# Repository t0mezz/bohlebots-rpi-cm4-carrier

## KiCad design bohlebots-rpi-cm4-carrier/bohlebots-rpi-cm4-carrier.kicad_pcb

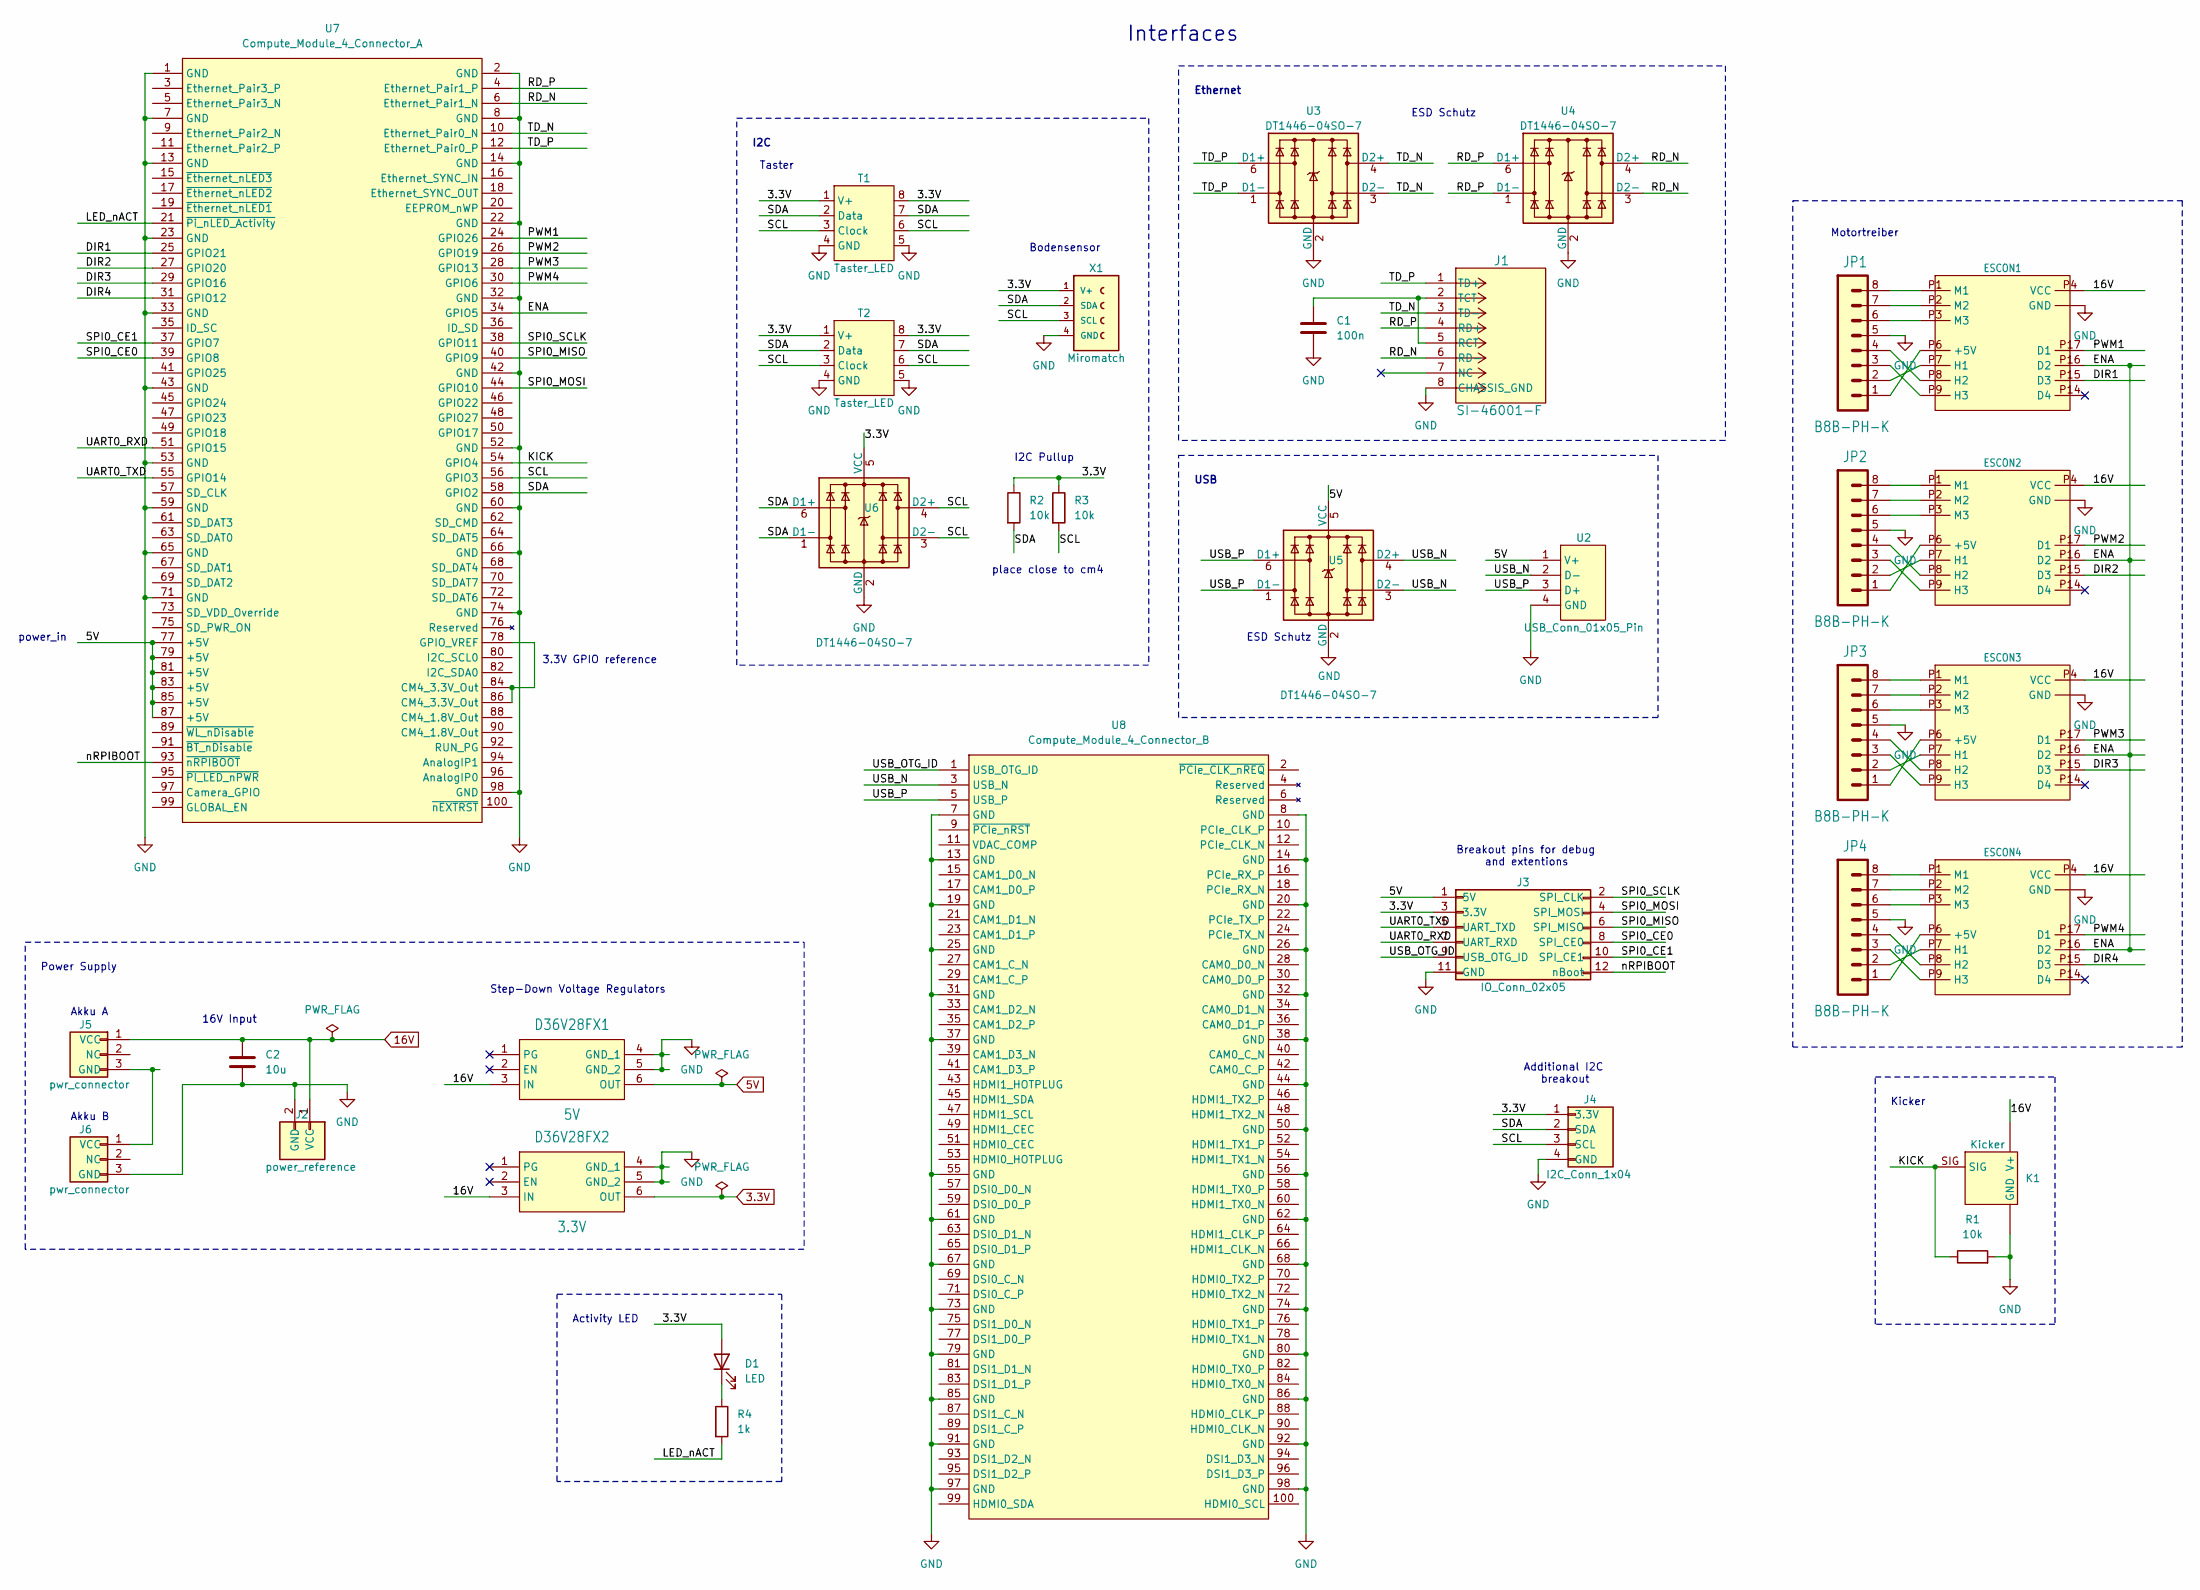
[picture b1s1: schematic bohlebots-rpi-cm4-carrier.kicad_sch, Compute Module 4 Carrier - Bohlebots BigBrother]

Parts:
C1: 100n; C_Radial_D5.0mm_H11.0mm_P2.00mm
C2: 10u; C_Radial_D5.0mm_H11.0mm_P2.00mm
D1: LED; LED_D5.0mm_FlatTop
D36V28FX1: 5V; D36V28FX
D36V28FX2: 3.3V; D36V28FX
ESCON1, ESCON2, ESCON3, ESCON4: 24_2; ESCOM_24_2
J1: SI-46001-F; CONN_46001-F_BEL
J2: power_reference; PinHeader_1x02_P2.54mm_Vertical
J3: IO_Conn_02x05; PinHeader_2x06_P2.54mm_Vertical
J4: I2C_Conn_1x04; PinHeader_1x04_P2.54mm_Vertical
J5, J6: pwr_connector; PinHeader_1x03_P2.54mm_Vertical
JP1, JP2, JP3, JP4: B8B-PH-K
K1: Kicker; KICKER
R1, R2, R3: 10k; R_Axial_DIN0207_L6.3mm_D2.5mm_P7.62mm_Horizontal
R4: 1k; R_Axial_DIN0207_L6.3mm_D2.5mm_P7.62mm_Horizontal
T1, T2: Taster_LED; TASTER_LED
U2: USB_Conn_01x05_Pin; PinHeader_1x04_P2.54mm_Vertical
U3, U4, U5, U6: DT1446-04SO-7; SOT26; Part Description Quad TVS diode for high speed signals (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
U7: Compute_Module_4_Connector_A; Hirose-DF40C-100DS-0.4V(51)
U8: Compute_Module_4_Connector_B; Hirose-DF40C-100DS-0.4V(51)
X1: Miromatch; MICROMATCH-4

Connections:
3.3V: D1.2 (A), D36V28FX2.6 (OUT), J3.3 (3.3V), J4.1 (3.3V), R2.1, R3.1, T1.1 (V+), T1.8, T2.1 (V+), T2.8, U6.5 (VCC), X1.1 (V+)
5V: D36V28FX1.6 (OUT), J3.1 (5V), U2.1 (V+), U5.5 (VCC), U7.77 (+5V), U7.79 (+5V), U7.81 (+5V), U7.83 (+5V), U7.85 (+5V), U7.87 (+5V)
16V: C2.1, D36V28FX1.3 (IN), D36V28FX2.3 (IN), ESCON1.P4 (VCC), ESCON2.P4 (VCC), ESCON3.P4 (VCC), ESCON4.P4 (VCC), J2.1 (VCC), J5.1 (VCC), K1.V+1 (V+), K1.V+2 (V+), K1.V+3 (V+)
/DIR1: ESCON1.P15 (D3), U7.25 (GPIO21)
/DIR2: ESCON2.P15 (D3), U7.27 (GPIO20)
/DIR3: ESCON3.P15 (D3), U7.29 (GPIO16)
/DIR4: ESCON4.P15 (D3), U7.31 (GPIO12)
/ENA: ESCON1.P16 (D2), ESCON2.P16 (D2), ESCON3.P16 (D2), ESCON4.P16 (D2), U7.34 (GPIO5)
/KICK: K1.SIG, R1.1, U7.54 (GPIO4)
/LED_nACT: R4.2, U7.21 (~Pi_nLED_Activity)
/PWM1: ESCON1.P17 (D1), U7.24 (GPIO26)
/PWM2: ESCON2.P17 (D1), U7.26 (GPIO19)
/PWM3: ESCON3.P17 (D1), U7.28 (GPIO13)
/PWM4: ESCON4.P17 (D1), U7.30 (GPIO6)
/RD_N: J1.6 (RD-), U4.3 (D2-), U4.4 (D2+), U7.6 (Ethernet_Pair1_N)
/RD_P: J1.4 (RD+), U4.1 (D1-), U4.6 (D1+), U7.4 (Ethernet_Pair1_P)
/SCL: J4.3 (SCL), R3.2, T1.3 (Clock), T1.6, T2.3 (Clock), T2.6, U6.3 (D2-), U6.4 (D2+), U7.56 (GPIO3), X1.3 (SCL)
/SDA: J4.2 (SDA), R2.2, T1.2 (Data), T1.7, T2.2 (Data), T2.7, U6.1 (D1-), U6.6 (D1+), U7.58 (GPIO2), X1.2 (SDA)
/SPI0_CE0: J3.8 (SPI_CE0), U7.39 (GPIO8)
/SPI0_CE1: J3.10 (SPI_CE1), U7.37 (GPIO7)
/SPI0_MISO: J3.6 (SPI_MISO), U7.40 (GPIO9)
/SPI0_MOSI: J3.4 (SPI_MOSI), U7.44 (GPIO10)
/SPI0_SCLK: J3.2 (SPI_CLK), U7.38 (GPIO11)
/TD_N: J1.3 (TD-), U3.3 (D2-), U3.4 (D2+), U7.10 (Ethernet_Pair0_N)
/TD_P: J1.1 (TD+), U3.1 (D1-), U3.6 (D1+), U7.12 (Ethernet_Pair0_P)
/UART0_RXD: J3.7 (UART_RXD), U7.51 (GPIO15)
/UART0_TXD: J3.5 (UART_TXD), U7.55 (GPIO14)
/USB_N: U2.2 (D-), U5.3 (D2-), U5.4 (D2+), U8.3 (USB_N)
/USB_OTG_ID: J3.9 (USB_OTG_ID), U8.1 (USB_OTG_ID)
/USB_P: U2.3 (D+), U5.1 (D1-), U5.6 (D1+), U8.5 (USB_P)
/nRPIBOOT: J3.12 (nBoot), U7.93 (~nRPIBOOT)
GND: C1.2, C2.2, D36V28FX1.4 (GND_1), D36V28FX1.5 (GND_2), D36V28FX2.4 (GND_1), D36V28FX2.5 (GND_2), ESCON1.P5 (GND), ESCON1.P18 (GND), ESCON2.P5 (GND), ESCON2.P18 (GND), ESCON3.P5 (GND), ESCON3.P18 (GND), ESCON4.P5 (GND), ESCON4.P18 (GND), J1.8 (CHASSIS_GND), J2.2 (GND), J3.11 (GND), J4.4 (GND), J6.3 (GND), JP1.5, JP2.5, JP3.5, JP4.5, K1.GND1 (GND), K1.GND2 (GND), K1.GND3 (GND), K1.GND4 (GND), K1.GND5 (GND), K1.GND6 (GND), K1.GND7 (GND), K1.GND8 (GND), R1.2, T1.4 (GND), T1.5, T2.4 (GND), T2.5, U2.4 (GND), U3.2 (GND), U4.2 (GND), U5.2 (GND), U6.2 (GND), U7.1 (GND), U7.2 (GND), U7.7 (GND), U7.8 (GND), U7.13 (GND), U7.14 (GND), U7.22 (GND), U7.23 (GND), U7.32 (GND), U7.33 (GND), U7.42 (GND), U7.43 (GND), U7.52 (GND), U7.53 (GND), U7.59 (GND), U7.60 (GND), U7.65 (GND), U7.66 (GND), U7.71 (GND), U7.74 (GND), U7.98 (GND), U8.7 (GND), U8.8 (GND), U8.13 (GND), U8.14 (GND), U8.19 (GND), U8.20 (GND), U8.25 (GND), U8.26 (GND), U8.31 (GND), U8.32 (GND), U8.37 (GND), U8.38 (GND), U8.44 (GND), U8.50 (GND), U8.55 (GND), U8.56 (GND), U8.61 (GND), U8.62 (GND), U8.67 (GND), U8.68 (GND), U8.73 (GND), U8.74 (GND), U8.79 (GND), U8.80 (GND), U8.85 (GND), U8.86 (GND), U8.91 (GND), U8.92 (GND), U8.97 (GND), U8.98 (GND), X1.4 (GND)
unnamed: D1.1 (K), R4.1
unnamed: ESCON1.P6 (+5V), JP1.1
unnamed: ESCON1.P7 (H1), JP1.2
unnamed: ESCON1.P8 (H2), JP1.4
unnamed: ESCON1.P9 (H3), JP1.3
unnamed: ESCON1.P1 (M1), JP1.8
unnamed: ESCON1.P2 (M2), JP1.7
unnamed: ESCON1.P3 (M3), JP1.6
unnamed: ESCON2.P6 (+5V), JP2.1
unnamed: ESCON2.P7 (H1), JP2.2
unnamed: ESCON2.P8 (H2), JP2.4
unnamed: ESCON2.P9 (H3), JP2.3
unnamed: ESCON2.P1 (M1), JP2.8
unnamed: ESCON2.P2 (M2), JP2.7
unnamed: ESCON2.P3 (M3), JP2.6
unnamed: ESCON3.P6 (+5V), JP3.1
unnamed: ESCON3.P7 (H1), JP3.2
unnamed: ESCON3.P8 (H2), JP3.4
unnamed: ESCON3.P9 (H3), JP3.3
unnamed: ESCON3.P1 (M1), JP3.8
unnamed: ESCON3.P2 (M2), JP3.7
unnamed: ESCON3.P3 (M3), JP3.6
unnamed: ESCON4.P6 (+5V), JP4.1
unnamed: ESCON4.P7 (H1), JP4.2
unnamed: ESCON4.P8 (H2), JP4.4
unnamed: ESCON4.P9 (H3), JP4.3
unnamed: ESCON4.P1 (M1), JP4.8
unnamed: ESCON4.P2 (M2), JP4.7
unnamed: ESCON4.P3 (M3), JP4.6
unnamed: C1.1, J1.2 (TCT), J1.5 (RCT)
unnamed: J5.3 (GND), J6.1 (VCC)
unnamed: U7.78 (GPIO_VREF), U7.84 (CM4_3.3V_Out), U7.86 (CM4_3.3V_Out)

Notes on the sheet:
ESD Schutz
Taster
USB
Power Supply
Interfaces
Bodensensor
Motortreiber
I2C Pullup
Akku B
Kicker
Ethernet
Breakout pins for debug and extentions
place close to cm4
Activity LED
3.3V GPIO reference
Akku A
power_in
I2C
Step-Down Voltage Regulators
Additional I2C breakout
16V Input

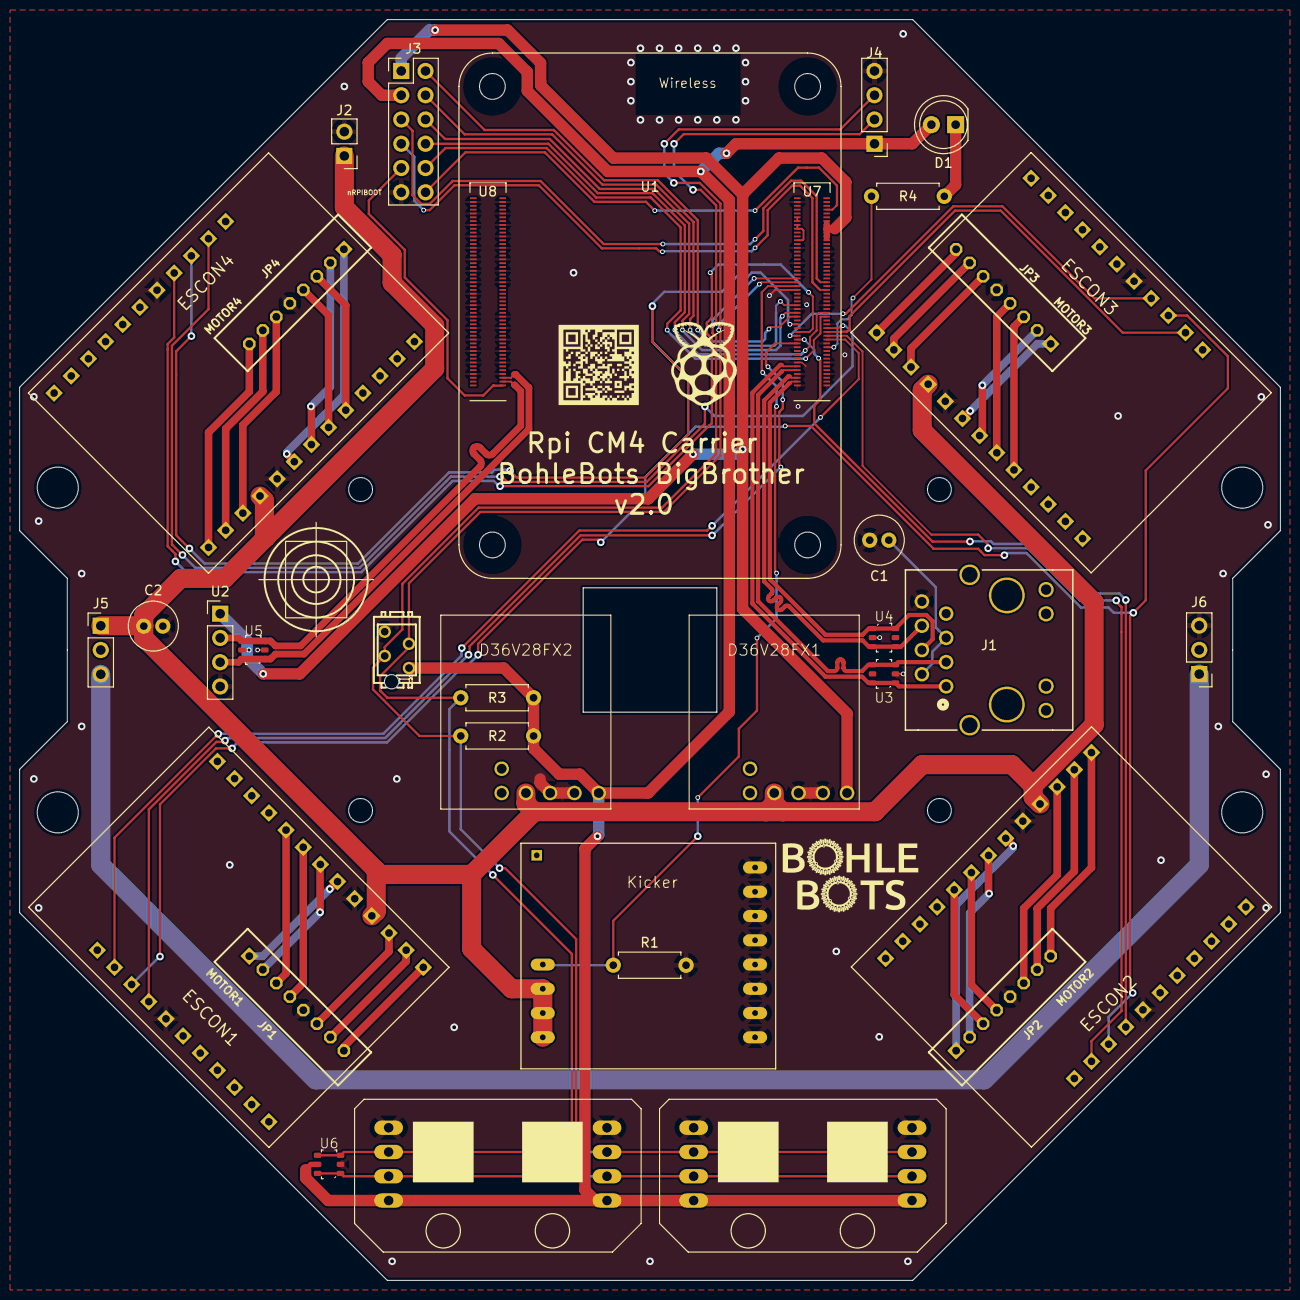
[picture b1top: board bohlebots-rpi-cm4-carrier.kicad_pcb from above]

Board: 2 copper layers, 132.0 x 132.0 mm, 37 parts (0 on the bottom side), 64 nets.

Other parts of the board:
Luxonis OAK-FFP 4P: Luxonis_OAK-FFC-4P_Foothold
REFe: MountingHole_4.3mm_M4
U1: Compute_Module_4_Connectors; Raspberry-Pi-4-Compute-Module

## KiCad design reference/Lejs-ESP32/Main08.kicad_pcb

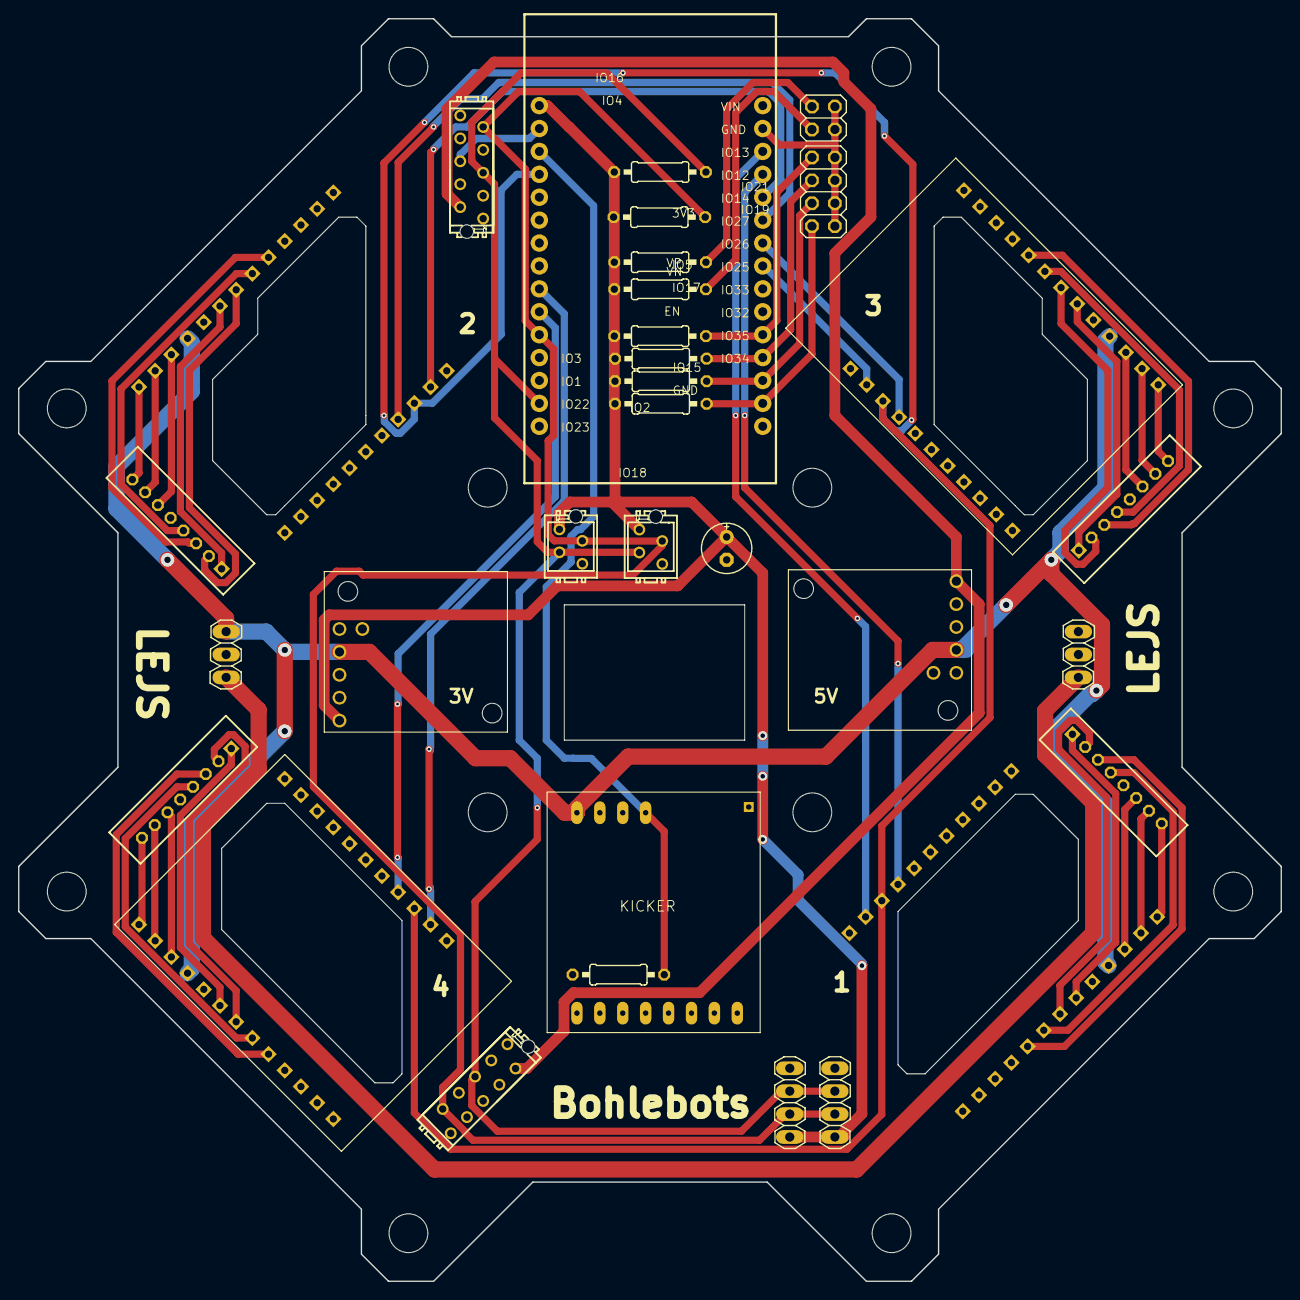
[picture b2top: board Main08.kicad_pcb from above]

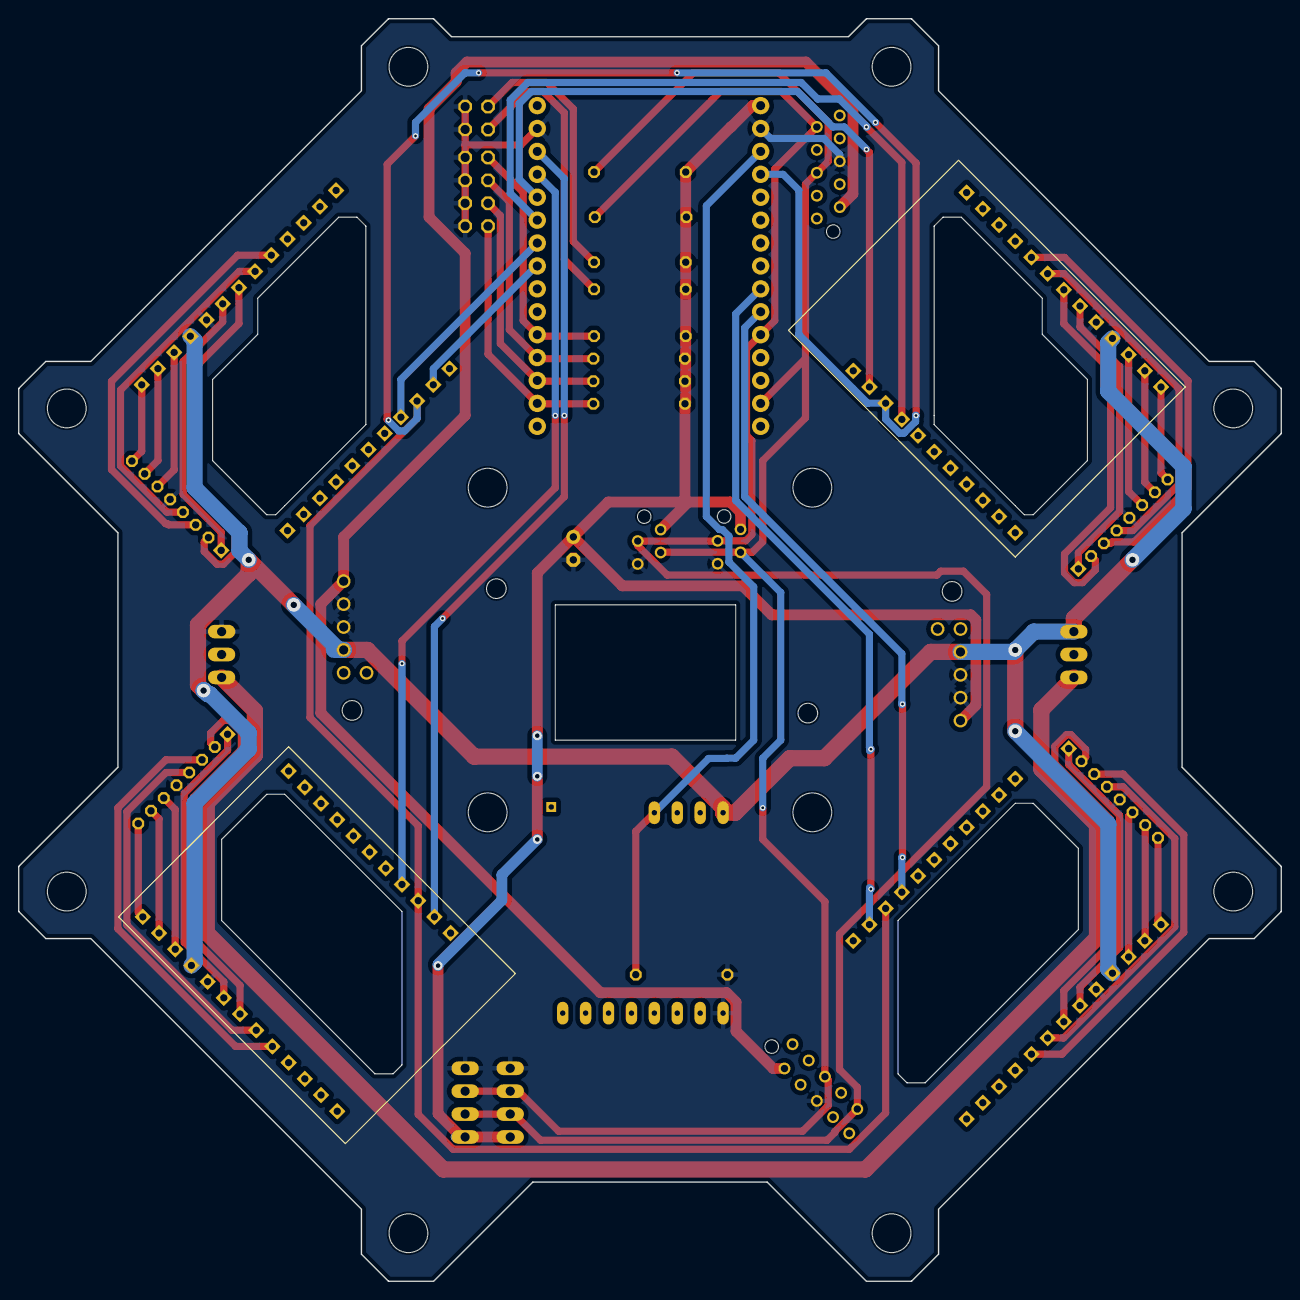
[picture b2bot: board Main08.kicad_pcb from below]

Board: 2 copper layers, 140.0 x 140.0 mm, 32 parts (2 on the bottom side), 51 nets.

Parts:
C1: 10µ; E2,5-6E
I2C_2, I2C_3: i2c-Bus; 1X04
IC1: D36V28FX; D36V28FX_3v
IC2: D36V28FX; D36V28FX_5V
JP1, JP4: Buchse; 1X03_8V
JP5, JP6, JP7, JP8: B8B-PH-K; B8B-PH-K_MS
JP13: led_out; 2X02_LS
JP14: Ana.input; 2X04_aP
R1, R2: 100; 0207_10_R
R3, R4, R5, R6, R9, R101: 10k; 0207_10_R
R108: 10K; 0207_10_R
U$1, U$2, U$3, U$4: 24/2; 24_2_MT
U$9: ESP32DEVKITV1; ESP32-DEVKITV1
U$17: KICKER
X1, X3: MICROMATCH-4; MICROMATCH-4_IR
X2, X5: MICROMATCH-10; MICROMATCH-10_Pixy

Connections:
+3V3: C1.+, I2C_2.1, I2C_3.1, IC1.6 (OUT), R1.1, R2.1, R3.1, R4.1, R5.1, R6.1, R9.1, R108.1, U$9.1 (3V3), X1.1 (S), X3.1 (S)
+5V: IC2.6 (OUT), X2.2 (S), X5.2 (S)
/CLOCK: I2C_2.3, I2C_3.3, R108.2, U$9.14 (IO22), X1.3 (S), X2.5 (S), X3.3 (S), X5.5 (S)
/DATA: I2C_2.2, I2C_3.2, R9.2, U$9.11 (IO21), X1.2 (S), X2.9 (S), X3.2 (S), X5.9 (S)
/DIR1: U$1.P15 (D3), U$9.28 (IO13)
/DIR2: U$2.P15 (D3), U$9.26 (IO14)
/DIR3: U$3.P15 (D3), U$9.23 (IO25)
/DIR4: U$4.P15 (D3), U$9.9 (IO18)
/ENA: U$1.P16 (D2), U$2.P16 (D2), U$3.P16 (D2), U$4.P16 (D2), U$9.4 (IO2)
/KICK: R101.1, U$9.3 (IO15), U$17.SIG
/PWM1: U$1.P17 (D1), U$9.27 (IO12)
/PWM2: U$2.P17 (D1), U$9.25 (IO27)
/PWM3: U$3.P17 (D1), U$9.24 (IO26)
/PWM4: U$4.P17 (D1), U$9.10 (IO19)
GND: C1.-, I2C_2.4, I2C_3.4, IC1.4 (GND_1), IC1.5 (GND_2), IC2.4 (GND_1), IC2.5 (GND_2), JP4.3, JP5.5, JP6.5, JP7.5, JP8.5, JP13.1, JP13.3, JP14.2, JP14.4, JP14.6, JP14.8, R101.2, U$1.P5 (GND), U$2.P5 (GND), U$3.P5 (GND), U$4.P5 (GND), U$9.2 (GND), U$9.29 (GND1), U$17.GND8 (GND), X1.4 (S), X2.6 (S), X3.4 (S), X5.6 (S)
unnamed: JP1.3, JP4.1
unnamed: JP13.2, R2.2
unnamed: JP13.4, R1.2
unnamed: JP5.1, U$1.P6 (+5V)
unnamed: JP5.2, U$1.P7 (H1)
unnamed: JP5.4, U$1.P8 (H2)
unnamed: JP5.3, U$1.P9 (H3)
unnamed: JP5.8, U$1.P1 (M1)
unnamed: JP5.7, U$1.P2 (M2)
unnamed: JP5.6, U$1.P3 (M3)
unnamed: JP6.1, U$2.P6 (+5V)
unnamed: JP6.2, U$2.P7 (H1)
unnamed: JP6.4, U$2.P8 (H2)
unnamed: JP6.3, U$2.P9 (H3)
unnamed: JP6.8, U$2.P1 (M1)
unnamed: JP6.7, U$2.P2 (M2)
unnamed: JP6.6, U$2.P3 (M3)
unnamed: JP7.1, U$3.P6 (+5V)
unnamed: JP7.2, U$3.P7 (H1)
unnamed: JP7.4, U$3.P8 (H2)
unnamed: JP7.3, U$3.P9 (H3)
unnamed: JP7.8, U$3.P1 (M1)
unnamed: JP7.7, U$3.P2 (M2)
unnamed: JP7.6, U$3.P3 (M3)
unnamed: JP8.1, U$4.P6 (+5V)
unnamed: JP8.2, U$4.P7 (H1)
unnamed: JP8.4, U$4.P8 (H2)
unnamed: JP8.3, U$4.P9 (H3)
unnamed: JP8.8, U$4.P1 (M1)
unnamed: JP8.7, U$4.P2 (M2)
unnamed: JP8.6, U$4.P3 (M3)
unnamed: JP14.3, R5.2, U$9.19 (IO34)
unnamed: JP14.1, R6.2, U$9.20 (IO35)
unnamed: JP14.5, R4.2, U$9.18 (VN)
unnamed: JP14.7, R3.2, U$9.17 (VP)
VCC: IC1.3 (IN), IC2.3 (IN), JP1.1, U$1.P4 (VCC), U$2.P4 (VCC), U$3.P4 (VCC), U$4.P4 (VCC), U$17.V+3 (V+)

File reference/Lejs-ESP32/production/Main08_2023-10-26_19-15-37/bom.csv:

Designator,Footprint,Quantity,Value,LCSC Part #
C1,"E2,5-6E",1,10µ,
"I2C_2, I2C_3",1X04,2,i2c-Bus,
IC1,D36V28FX_3v,1,D36V28FX,
IC2,D36V28FX_5V,1,D36V28FX,
"JP1, JP4",1X03_8V,2,Buchse,
JP13,2X02_LS,1,led_out,
JP14,2X04_aP,1,Ana.input,
"JP5, JP6, JP7, JP8",B8B-PH-K_MS,4,B8B-PH-K,
"R1, R2",0207_10_R,2,100,
"R101, R108, R3, R4, R5, R6, R9",0207_10_R,7,10k,
"U$1, U$2, U$3, U$4",24_2_MT,4,24/2,
U$17,KICKER,1,KICKER,
U$9,ESP32-DEVKITV1,1,ESP32DEVKITV1,
"X1, X3",MICROMATCH-4_IR,2,MICROMATCH-4,
"X2, X5",MICROMATCH-10_Pixy,2,MICROMATCH-10,

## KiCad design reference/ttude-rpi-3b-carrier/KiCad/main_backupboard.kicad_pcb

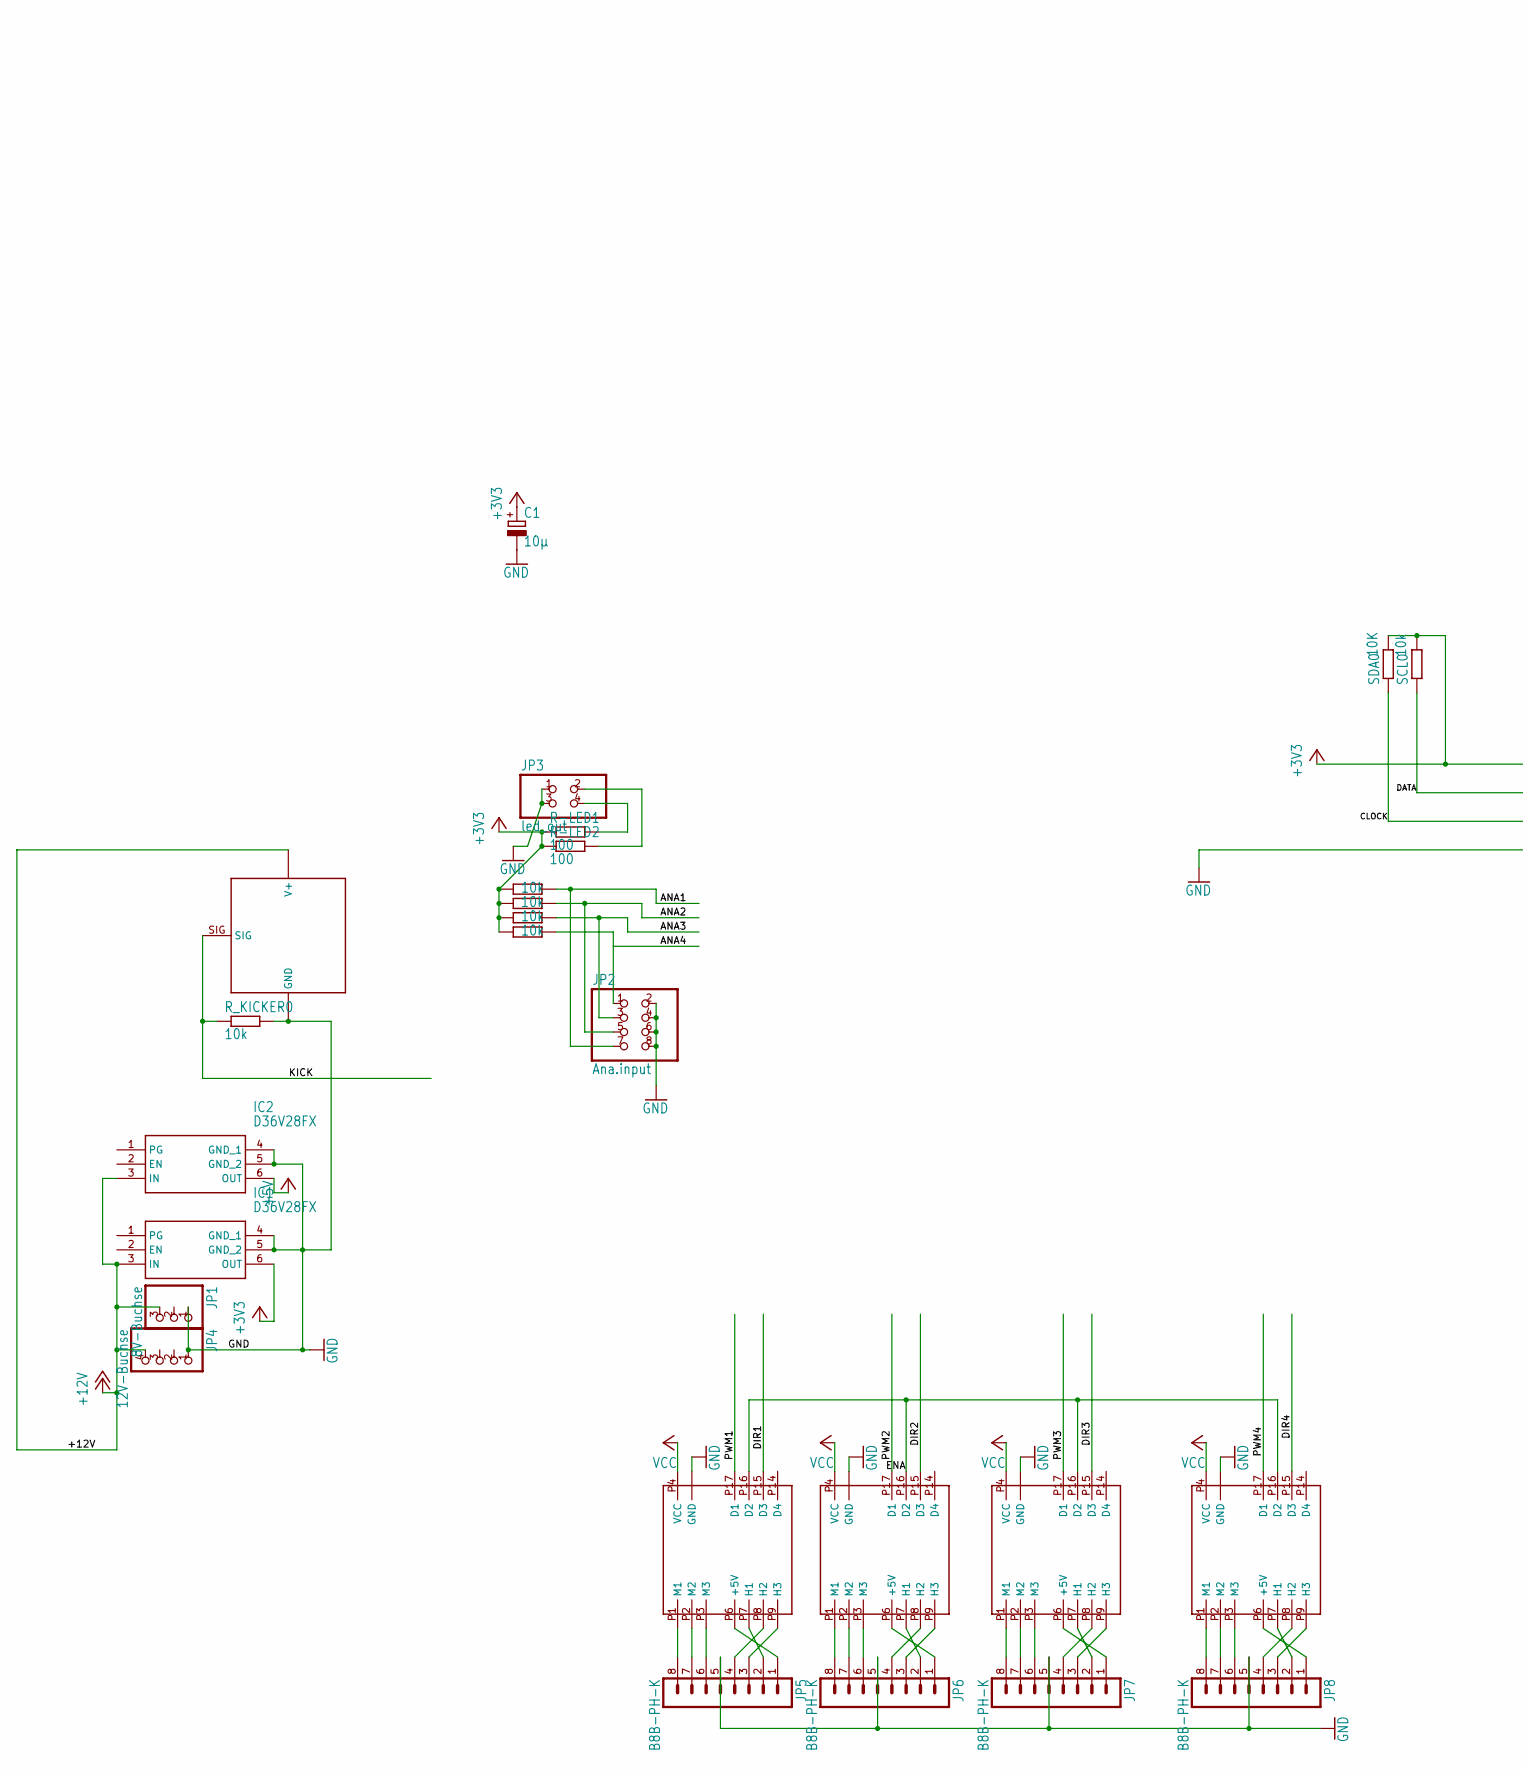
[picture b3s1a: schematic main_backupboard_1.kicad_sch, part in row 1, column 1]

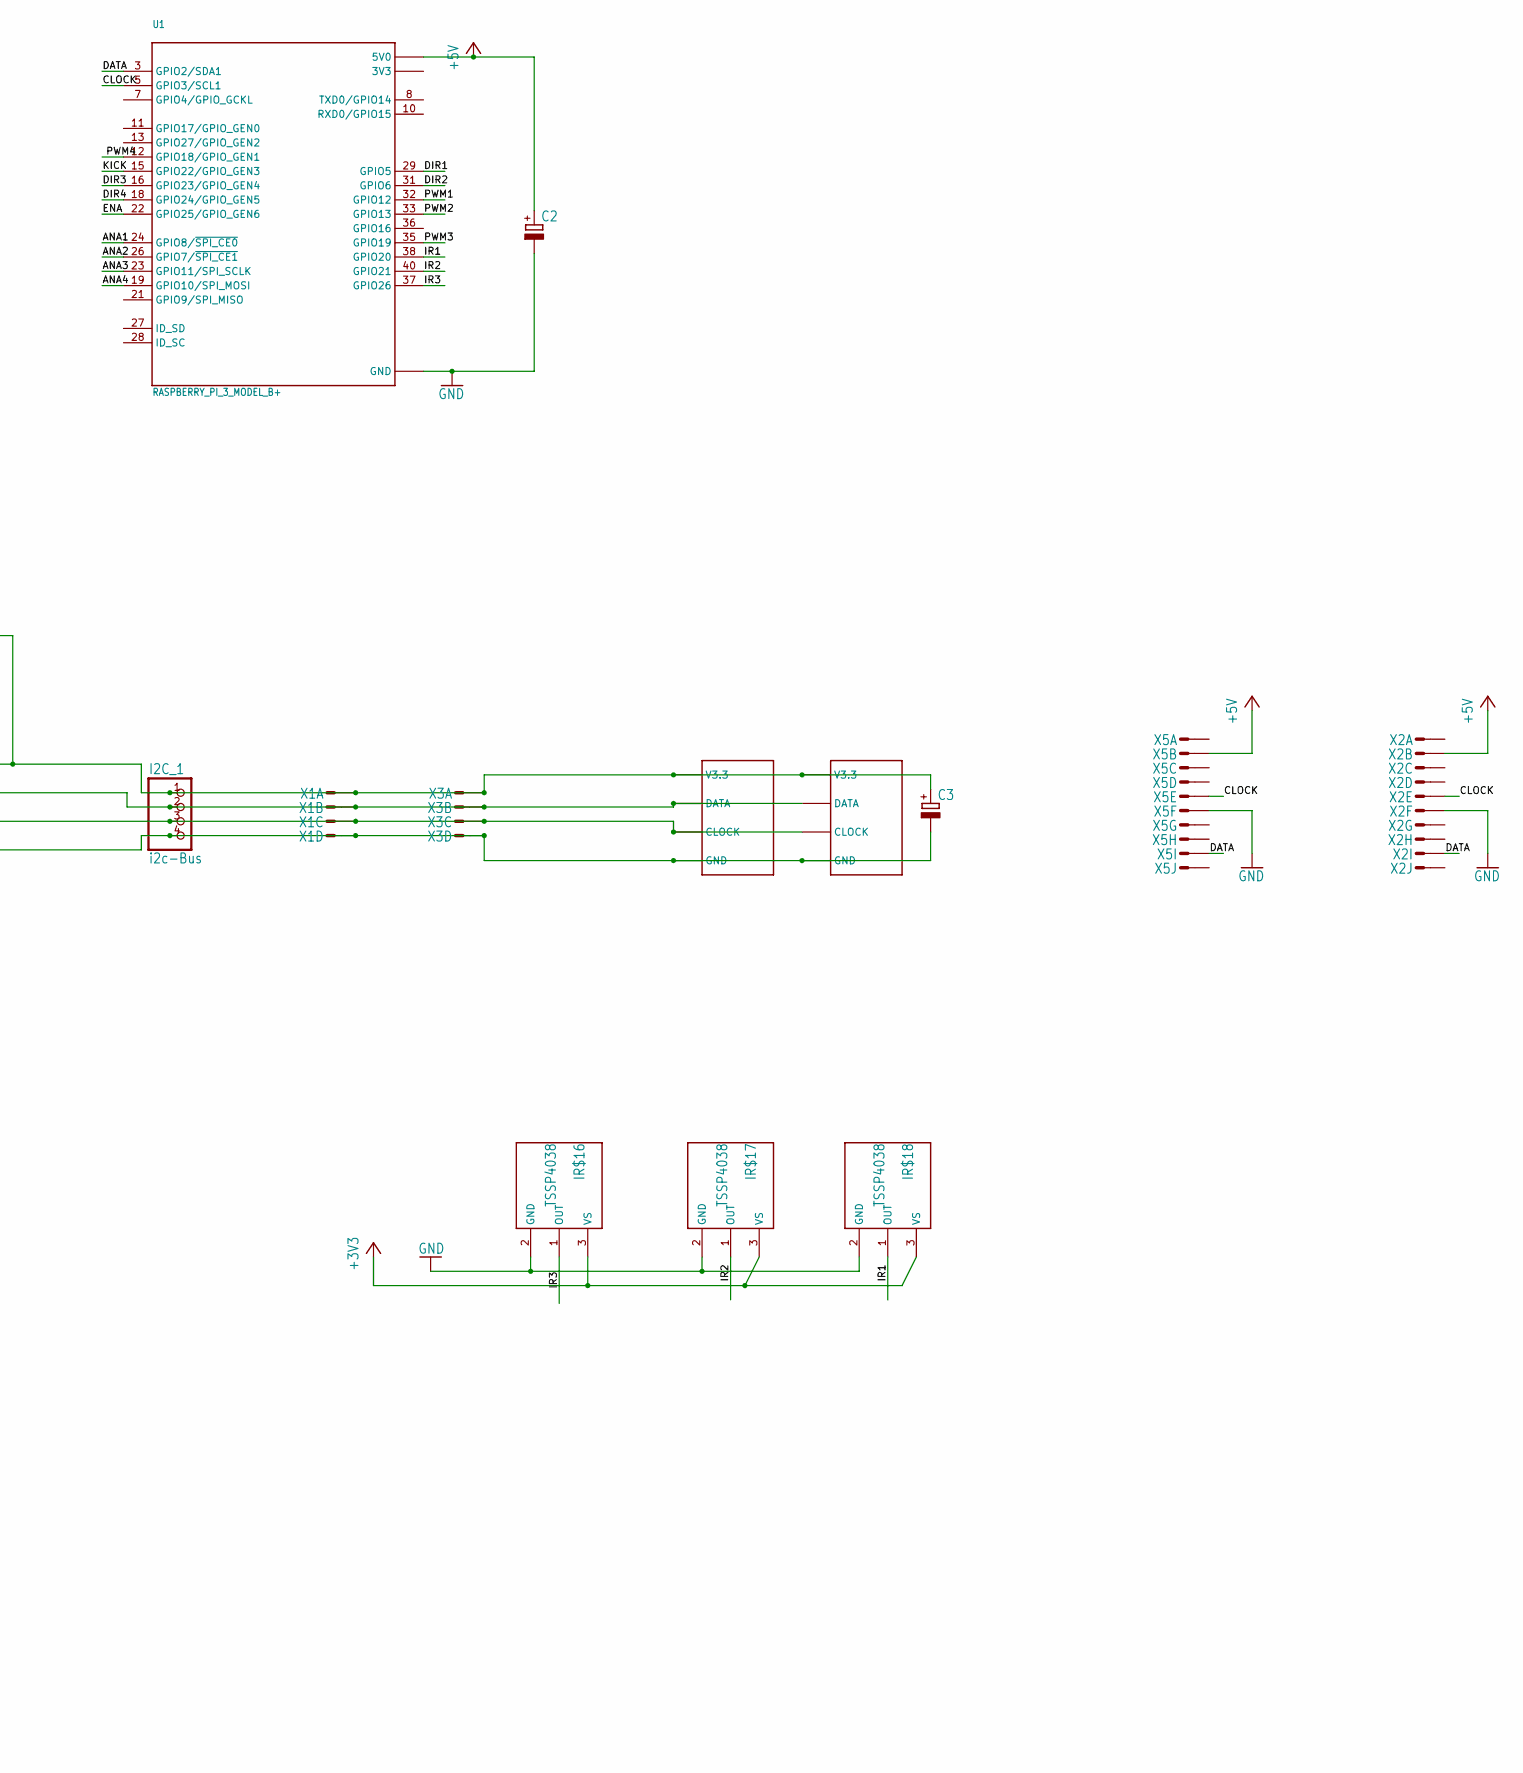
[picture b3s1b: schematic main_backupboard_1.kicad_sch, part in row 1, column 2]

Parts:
C1: 10µ; E2,5-6E
C2, C3: CPOL-EUE2-5; E2-5
I2C_1: i2c-Bus; 1X04
IC1, IC2: D36V28FX
IR$16, IR$17, IR$18: TSSP4038; XDCR_TSSP4038
JP1: 8V-Buchse; 1X03
JP2: Ana.input; 2X04
JP3: led_out; 2X02
JP4: 12V-Buchse; 1X04
JP5, JP6, JP7, JP8: B8B-PH-K
R-LED1, R-LED2: 100; 0207_10
R_AD14, R_AD25, R_AD26, R_AD27: 10k; 0207_10
R_KICKER0: 10k; 0207_10
SCL0: 10k; 0207_10
SDA0: 10K; 0207_10
U1: RASPBERRY_PI_3_MODEL_B+; MODULE_RASPBERRY_PI_3_MODEL_B+
U$1, U$2, U$3, U$4: 24/2; 24_2
U$8, U$9: TASTER_LED
U$17: KICKER
X1, X3: MICROMATCH-4
X2, X5: MICROMATCH-10

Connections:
3V3: U1.1 (3V3), U1.17 (3V3)
+3V3: C1.+, C3.+, I2C_1.1, IC1.6 (OUT), IR$16.3 (VS), IR$17.3 (VS), IR$18.3 (VS), R-LED1.1, R-LED2.1, R_AD14.1, R_AD25.1, R_AD26.1, R_AD27.1, SCL0.2, SDA0.2, U$8.V1 (V3.3), U$8.V2 (V3.3), U$9.V1 (V3.3), U$9.V2 (V3.3), X1.1, X3.1
+5V: C2.+, IC2.6 (OUT), U1.2 (5V0), U1.4 (5V0), X2.2, X5.2
ANA1: JP2.7, R_AD25.2, U1.24 (GPIO8/~SPI_CE0)
ANA2: JP2.5, R_AD26.2, U1.26 (GPIO7/~SPI_CE1)
ANA3: JP2.3, R_AD27.2, U1.23 (GPIO11/SPI_SCLK)
CLOCK: I2C_1.3, SDA0.1, U1.5 (GPIO3/SCL1), U$8.C1 (CLOCK), U$8.C2 (CLOCK), U$9.C1 (CLOCK), U$9.C2 (CLOCK), X1.3, X2.5, X3.3, X5.5
DATA: I2C_1.2, SCL0.1, U1.3 (GPIO2/SDA1), U$8.D1 (DATA), U$8.D2 (DATA), U$9.D1 (DATA), U$9.D2 (DATA), X1.2, X2.9, X3.2, X5.9
DIR1: U1.29 (GPIO5), U$4.P15 (D3)
DIR2: U1.31 (GPIO6), U$3.P15 (D3)
DIR3: U1.16 (GPIO23/GPIO_GEN4), U$1.P15 (D3)
DIR4: U1.18 (GPIO24/GPIO_GEN5), U$2.P15 (D3)
ENA: U1.22 (GPIO25/GPIO_GEN6), U$1.P16 (D2), U$2.P16 (D2), U$3.P16 (D2), U$4.P16 (D2)
GND: C1.-, C2.-, C3.-, I2C_1.4, IC1.4 (GND_1), IC1.5 (GND_2), IC2.4 (GND_1), IC2.5 (GND_2), IR$16.2 (GND), IR$17.2 (GND), IR$18.2 (GND), JP1.1, JP2.2, JP2.4, JP2.6, JP2.8, JP3.1, JP3.3, JP4.1, JP5.5, JP6.5, JP7.5, JP8.5, R_KICKER0.2, U1.6 (GND), U1.9 (GND), U1.14 (GND), U1.20 (GND), U1.25 (GND), U1.30 (GND), U1.34 (GND), U1.39 (GND), U$1.P5 (GND), U$1.P18 (GND), U$2.P5 (GND), U$2.P18 (GND), U$3.P5 (GND), U$3.P18 (GND), U$4.P5 (GND), U$4.P18 (GND), U$8.G1 (GND), U$8.G2 (GND), U$9.G1 (GND), U$9.G2 (GND), U$17.GND1 (GND), U$17.GND2 (GND), U$17.GND3 (GND), U$17.GND4 (GND), U$17.GND5 (GND), U$17.GND6 (GND), U$17.GND7 (GND), U$17.GND8 (GND), X1.4, X2.6, X3.4, X5.6
IR1: IR$18.1 (OUT), U1.38 (GPIO20)
IR2: IR$17.1 (OUT), U1.40 (GPIO21)
IR3: IR$16.1 (OUT), U1.37 (GPIO26)
KICK: R_KICKER0.1, U1.15 (GPIO22/GPIO_GEN3), U$17.SIG
unnamed: JP5.8, U$4.P1 (M1)
unnamed: JP5.7, U$4.P2 (M2)
unnamed: JP3.4, R-LED1.2
unnamed: JP3.2, R-LED2.2
unnamed: JP5.6, U$4.P3 (M3)
unnamed: JP6.8, U$3.P1 (M1)
unnamed: JP6.7, U$3.P2 (M2)
unnamed: JP6.6, U$3.P3 (M3)
unnamed: JP7.8, U$1.P1 (M1)
unnamed: JP7.7, U$1.P2 (M2)
unnamed: JP7.6, U$1.P3 (M3)
unnamed: JP8.8, U$2.P1 (M1)
unnamed: JP8.7, U$2.P2 (M2)
unnamed: JP8.6, U$2.P3 (M3)
unnamed: JP5.1, U$4.P6 (+5V)
unnamed: JP6.1, U$3.P6 (+5V)
unnamed: JP7.1, U$1.P6 (+5V)
unnamed: JP8.1, U$2.P6 (+5V)
unnamed: JP5.2, U$4.P7 (H1)
unnamed: JP5.3, U$4.P9 (H3)
unnamed: JP5.4, U$4.P8 (H2)
unnamed: JP6.2, U$3.P7 (H1)
unnamed: JP6.3, U$3.P9 (H3)
unnamed: JP6.4, U$3.P8 (H2)
unnamed: JP7.2, U$1.P7 (H1)
unnamed: JP7.3, U$1.P9 (H3)
unnamed: JP7.4, U$1.P8 (H2)
unnamed: JP8.2, U$2.P7 (H1)
unnamed: JP8.3, U$2.P9 (H3)
unnamed: JP8.4, U$2.P8 (H2)
PWM1: U1.32 (GPIO12), U$4.P17 (D1)
PWM2: U1.33 (GPIO13), U$3.P17 (D1)
PWM3: U1.35 (GPIO19), U$1.P17 (D1)
PWM4: U1.12 (GPIO18/GPIO_GEN1), U$2.P17 (D1)

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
